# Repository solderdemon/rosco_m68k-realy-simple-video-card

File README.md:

# SolderDemon m68k Really Simple Video

## Overview

A SolderDemon m68k expansion card with a 640 × 480 monochrome framebuffer, 60 Hz VGA output, and two display pages. Two ATF1502AS CPLDs handle video timing, memory addressing, and the host interface.

J1 matches the expansion bus pinout of [rosco_m68k r2](https://github.com/rosco-m68k/rosco_m68k).

**Status.** r1 fabrication files and CPLD programming files are available. The CPLD fit and logic have been verified. Hardware verification is pending.

## Start here

- [KiCad project](design/solderdemon_m68k-realy-simple-video-card.kicad_pro)
- [Schematic (PDF)](manufacturing/solderdemon_m68k-realy-simple-video-card-schematic.pdf)
- [Assembly and bring-up](docs/BRINGUP.md)
- [Gerbers and drill files](manufacturing/solderdemon_m68k-realy-simple-video-card-gerbers.zip)

## Board views

| Top | Bottom |
|:---:|:---:|
|  |  |

## Hardware

### Features

| | |
|---|---|
| Picture | 640 × 480, 1 bit per pixel, two pages; 80 × 60 characters of 8 × 8 |
| Video signal | VGA, 31.25 kHz / 59.5 Hz from a 25.000 MHz can — VESA 640 × 480 @ 60 Hz geometry, 0.7 % slow |
| VRAM | `$A00001 + 2n`, byte n = page << 16 \| y << 7 \| x >> 3; byte access through `/LDS`, no wait states |
| Register | `$B00001` — write b0 video on, b1 page shown; read b0 VBLANK, b1 HBLANK |
| Logic | 2 × ATF1502AS-10JU44 (PLCC-44), one JTAG chain on `J3`; address multiplexer inside |
| Memory | one AS6C1008 128K SRAM, 55–100 ns |
| Data path | 74HCT245 transceiver, 74HC166 serialiser, 2N3904 video buffer |
| Power | 5 V from the bus, ~120–200 mA |
| Assembly | through-hole, every IC socketed; two CPLDs to program over JTAG |
| Size | 92 × 96 mm, 2 layers |

### Two CPLDs, five ICs

An ATF1502AS has 32 macrocells and, with JTAG left enabled, 28 I/O pins plus 4 dedicated inputs —
**32 usable signals**. An address multiplexer alone is 16 inputs plus 16 outputs: 32 pins before
any logic. The card therefore **splits the counters along with the multiplexer halves**, so that
no counter bit ever crosses between the two devices:

| | Holds | Drives | Pins | Macrocells |
|:---|:---|:---|:---:|:---:|
| **U1** | byte counter B, pixel phase, bus decode, control bit "video on", status | MA0–MA6, /HSYNC, /LOAD, /SEL, /SRAM_WE, /BUF_OE, /DTACK, D0, D1 | 32/32 | 30/32 |
| **U2** | line counter L, page register | MA7–MA16, /VSYNC, VBLANK | 30/32 | 30/32 |

Only three wires run between them: `SEL_N`, `LEND` (step the line counter) and `VBLANK`.

- **The control register is synchronous.** It is sampled on every 25 MHz clock while the write
  strobe is low, so it does not depend on the 68010's data hold time.
- **The address path is short.** The CPU's address reaches the SRAM through one CPLD (~10 ns),
  and the video address never leaves the chip that counts it.

### Display and memory

- **Video mode:** 640 × 480 @ 59.52 Hz, 31.250 kHz, exact VESA timing from a 25.000 MHz canned
  oscillator (`X1`) — 16/96/48 clock porches, VSYNC on lines 490-491; the clock leaves `X1`
  through two 33 Ω series resistors (`R7` to the CPLDs, `R8` to `U5`)
- **Framebuffer:** two pages of 480 × 128 bytes in one AS6C1008 (`U3`)
- **Direct CPU access:** VRAM at `$A00001 + 2n` (n = page << 16 | y << 7 | x >> 3), byte access
  through `/LDS`, zero wait states; the CPU reaches both pages at any time
- **Control & status:** one register at `$B00001` — write video on/off and the displayed page,
  read VBLANK and HBLANK
- **Programmable logic:** 2 × ATF1502AS-10JU44 (`U1`, `U2`) in one JTAG chain on `J3`
- **Data path:** 74HCT245 transceiver (`U4`), 74HC166 pixel serialiser (`U5`), `Q1` video emitter follower
- **Video output:** the pixel bit drives `Q1`, an emitter follower, which feeds R, G and B through
  390 Ω (`R1`–`R3`, ~0.67 V into 75 Ω); 47 Ω sync resistors (`R4`, `R5`) to a DE-15 HD socket
  (`J2`). Fit only `R2` for a green screen, `R1` + `R2` for amber — the brightness does not change
- **Power:** +5 V from the expansion bus, ~120–200 mA; 100 nF bypass at every IC (`C1`–`C8`),
  47 µF bulk capacitor (`C9`)
- **Form factor:** 92 × 96 mm 2-layer PCB, right-angle bus socket (`J1`) along the right edge

### Pinout

#### J1 — SolderDemon m68k Expansion Bus (signals used by the card)

| Pin | Signal | Use | Pin | Signal | Use |
|:---:|:---|:---|:---:|:---|:---|
| **1–13 (odd)** | **A1–A7** | to U1, the low address half | **2** | **VCC** | +5 V supply |
| **15–33 (odd)** | **A8–A17** | to U2, the high address half | **6** | **GND** | Ground |
| **39** | **A20** | VRAM (0) / register (1) select | **18** | **~EXPSEL** | Expansion space select (includes `/AS`) |
| **41, 45** | **A21, A23** | Card window decode | **32** | **~LDS** | Byte data strobe |
| **61, 63, 64, 62** | **D0–D3** | Data bus via `U4` | **36** | **~RESET** | Clears the control register |
| **60, 58, 56, 54** | **D4–D7** | Data bus via `U4` | **59** | **R/~W** | Read / write |
| **57** | **~DTACK** | Pulled low by `U1` | | | |

A22 is not decoded (under `/EXPSEL` the only range with A23 and A21 set is `$A00000-$BFFFFF`), and
A18/A19 are unconnected, so the VRAM image repeats through `$A40000–$AFFFFF`.

#### J2 — VGA (DE-15 HD, female)

| Pin | Signal | Description |
|:---:|:---|:---|
| **1, 2, 3** | **RED, GREEN, BLUE** | ~0.62 V into 75 Ω, all three from the same pixel bit |
| **13, 14** | **HSYNC, VSYNC** | Active low, 47 Ω series resistors |
| **5–8, 10, shell** | **GND** | Ground |
| **4, 9, 11, 12, 15** | — | Not connected (no DDC) |

#### J3 — JTAG (Atmel 10-pin ISP)

| Pin | Signal | Pin | Signal |
|:---:|:---|:---:|:---|
| 1 | TCK | 2 | GND |
| 3 | TDO | 4 | VCC (+5 V) |
| 5 | TMS | 6–8 | not connected |
| 9 | TDI | 10 | GND |

The two devices sit in one chain: TDI → U1 → U2 → TDO.

#### Memory map

| Address | R/W | Description |
|:---|:---:|:---|
| `$A00001 + 2n` | R/W | VRAM byte n = page << 16 \| y << 7 \| x >> 3 (128 bytes per row, 80 visible; bit 7 is the leftmost pixel) |
| `$B00001` | W | b0 video on, b1 page shown; system reset clears both (black screen, page 0) |
| `$B00001` | R | b0 VBLANK, b1 HBLANK (1 = in blanking); b2–b7 undefined, mask them |

The register repeats over `$B00001–$BFFFFF`. Even addresses in `$A00000–$BFFFFF` end in a bus
error. Any CPU access while the picture is on shows eight wrong pixels on the current scanline
("snow"), so draw on the hidden page and `video_flip()`, or draw inside VBLANK.

This window does not overlap `rosco_m68k-simple-video` (`$800000–$9FFFFF`), so both cards can sit
on the same backplane. Check it against your RAM expansion, which also lives in expansion space.

## Using the board

### Software

```c
#include "video.h"

video_init();                                   /* video off, page 0 */
video_clear(0);
video_text(2, 2, "SolderDemon m68k Really Simple Video");
video_rect(0, 0, 640, 480, 1);
video_show(0, true);

video_draw_page(1);                             /* draw on the hidden page... */
video_clear(0);
video_fill(100, 80, 96, 64, 1);
video_flip();                                   /* ...and show it at the next VBLANK */
```

Without the driver, `*(uint8_t *)(0xA00001 + (y << 8) + ((x >> 3) << 1)) |= 0x80 >> (x & 7);`
sets a pixel on page 0. The driver (`code/software/video.c/.h`) adds clipping, lines, fills, an 8 × 8
console font (80 × 60 characters), page flipping and a full VRAM self test; `code/software/main.c` is a
text-page and bouncing-box demo.

## Build and verification

### Bill of Materials

| Reference | Value | Package / Footprint | Notes |
|:---|:---|:---|:---|
| **U1** | ATF1502AS-10JU44 | PLCC-44, THT socket | Bus, byte counter, MA0–MA6 — `code/firmware/cpld/rsv_u1.pld` |
| **U2** | ATF1502AS-10JU44 | PLCC-44, THT socket | Line counter, MA7–MA16, page — `code/firmware/cpld/rsv_u2.pld` |
| **U3** | AS6C1008-55PCN | DIP-32, 600 mil | 128K SRAM, 55–100 ns |
| **U4** | 74HCT245 | DIP-20 | Data bus transceiver |
| **U5** | 74HC166 | DIP-16 | Pixel serialiser |
| **X1** | 25.000 MHz | Oscillator DIP-8, 5 V | Canned oscillator (not a crystal) |
| **J1** | Conn_02x32 | PinSocket 2×32, 2.54 mm, Horizontal | SolderDemon m68k expansion bus |
| **J2** | DE-15 HD | DSUB-15-HD Socket, Horizontal | VGA output |
| **J3** | 2×5 pin header | 2.54 mm | Atmel JTAG / ISP |
| **Q1** | 2N3904 | TO-92 | Video emitter follower (BC547, BC337, 2N2222 all fine) |
| **R1–R3** | 390 Ω | Axial DIN0207, P7.62 mm | Video R, G, B |
| **R6** | 220 Ω | Axial DIN0207, P7.62 mm | Base resistor for Q1 |
| **R4, R5** | 47 Ω | Axial DIN0207, P7.62 mm | HSYNC / VSYNC series resistors |
| **R7, R8** | 33 Ω | Axial DIN0207, P7.62 mm | Clock series resistors at X1: R7 to the CPLDs, R8 to U5 |
| **C1–C8** | 100 nF | Radial 5.08 mm pitch | Bypass: two per CPLD, one per other IC, one at the oscillator |
| **C9** | 47 µF 10 V | Radial D6.3 mm, P2.5 mm | Bulk capacitor |
| — | Sockets | 2 × PLCC-44 THT, 1 × DIP-32 (600 mil), 1 × DIP-20, 1 × DIP-16, 1 × DIP-8 | Every IC is socketed |

You will also need a **JTAG programmer** — a USB Blaster clone is enough — and Microchip's WinCUPL
plus the ATF150x fitter.

The shift register stays discrete because neither CPLD has eight spare pins for MD0–MD7. It is an
ordinary **74HC166**: Nexperia specify that part at 40 MHz over the full temperature range at
4.5 V, so 25.000 MHz has plenty of margin.

Three 75 Ω monitor inputs want 9.3 mA each at full white, about 26 mA from one driver, and no
74HC/HCT output is rated for that (74HC166: IOH 4 mA, 20 mA absolute maximum). So `Q1` is an
emitter follower: U5 drives its base through `R6` at a few hundred microamps and `Q1` supplies the
current. `R1`–`R3` then set the level on their own, which is why leaving one out changes the
colour but not the brightness.

### Design files

- **KiCad project:** `design/solderdemon_m68k-realy-simple-video-card.kicad_pro` / `.kicad_sch` / `.kicad_pcb`
- **CPLD firmware:** [code/firmware/cpld/rsv_u1.pld](code/firmware/cpld/rsv_u1.pld), [code/firmware/cpld/rsv_u2.pld](code/firmware/cpld/rsv_u2.pld) —
  CUPL sources; they are also the single source of each CPLD's pinout, read by the generator and
  the simulator
- **Manufacturing outputs:** [manufacturing/](manufacturing) — Gerbers, drill file, placement
  file, schematic PDF, BOM
- **PCB specs:** 2 layers, 92 × 96 mm, 1.6 mm FR-4, 1 oz copper, 0.2 mm minimum track and
  clearance, 0.3 mm minimum hole, GND pour on both layers
- **Software:** [code/software/](code/software) — driver `video.c/.h`, font `font8x8.c`, demo `main.c`,
  Makefile; [code/tests/test_driver.c](code/tests/test_driver.c) host test
- **Generators:** [tools/](tools) — `build_card.py`, `route_card.py`, `sim_card.py` + `cupl.py`,
  `make_font.py`
- **Design documentation:** [docs/DESIGN.md](docs/DESIGN.md) (how the split works),
  [docs/BRINGUP.md](docs/BRINGUP.md) (programming, assembly, first power-up),
  [docs/BUILD.md](docs/BUILD.md) (regenerating everything)

### Verification

- **ERC:** 0 errors, 0 warnings ([erc.rpt](erc.rpt)).
- **DRC with schematic parity:** 0 violations at error *and* warning severity, 0 unconnected pads
  ([drc.rpt](drc.rpt)).
- **Routing:** 1154 tracks and vias, 68 vias, GND pour on both layers.
- **Netlist simulation** ([sim-verification.txt](sim-verification.txt), 31/31 pass): both counters
  run their full cycles and recover from all 128/1024 power-up states; the raster is 800 clocks ×
  525 lines with HSYNC at clocks 664–759 and VSYNC on lines 490–491; VRAM writes and reads on both
  pages; the control register split across the two chips, and the status read; `/DTACK` only
  inside the window; no bus contention. Two checks are specific to r1: **MA0..MA16 is compared
  against the expected address on every clock of a frame**, which is what proves the two address
  halves agree, and all 307200 pixels of a frame are compared with the SRAM, then again after a
  page flip. The simulator runs the real `.pld` files through `tools/cupl.py`.
- **CPLD fit** (`code/firmware/cpld/build.sh`, `code/firmware/cpld/bin/*.fit`, `*.jed`): both designs fit with every pin where
  the `.pld` — and therefore the PCB — puts it; U1 32/32 pins and 30/32 macrocells, U2 30/32 and
  30/32. `tools/check_fit.py` then compares the fitter's sum-of-products equations with the
  `cupl.py` model the simulation ran (every output, enable and next state, 200000 random vectors
  each): they match. This check found that CUPL reads `!FIELD:[lo..hi]` as "the complemented
  field is in range", which had turned both sync pulses into nonsense in the compiled logic while
  the simulation passed; the `.pld` files now write `!(FIELD:[..])` and `cupl.py` follows CUPL.
- **Driver** ([driver-verification.txt](driver-verification.txt), 31/31 pass): the real `video.c`
  against a model of the card, including the self test catching a stuck page address line.
- **NOT verified — read this before ordering a board:**
  - Timing has only been checked on paper, including the one-clock BUFD delay that lets the SRAM
    and the 74HCT245 share MD, and the LEND hand-off between the two chips.
  - No PCB has been manufactured; no build with the m68k toolchain; monitor compatibility unknown.

<!-- repository-layout -->
## Repository layout

- [`design/`](design/solderdemon_m68k-realy-simple-video-card.kicad_pro): KiCad project, schematic sheets, PCB, local libraries and design data. Open the project directly here.
- [`code/firmware/`](code/firmware/): ROM and programmable-logic sources and programming files.
- [`code/software/`](code/software/): drivers, examples and applications.
- [`code/build/`](code/build/): local build products; ignored by Git except for its README.
- [`tools/`](tools/): generators, simulations and export scripts. Run commands from the repository root unless stated otherwise.
- [`manufacturing/`](manufacturing/): fabrication packages.

Programmable-logic files are in `code/firmware/cpld/`. Native CPLD tools retain their adjacent `bin/` outputs.
Design files and documentation are generated by scripts in `tools/`; change the sources and regenerate. Keep `.kicad_pro` as the source of DRC rules.
<!-- /repository-layout -->

## Licences and attribution

Copyright © 2026 SolderDemon.

- **Hardware** — [CERN Open Hardware Licence v1.2](LICENCE.hardware.txt).
- **Documentation** — [Creative Commons Attribution 4.0](https://creativecommons.org/licenses/by/4.0/).

Third-party materials retain their original notices and licence terms.

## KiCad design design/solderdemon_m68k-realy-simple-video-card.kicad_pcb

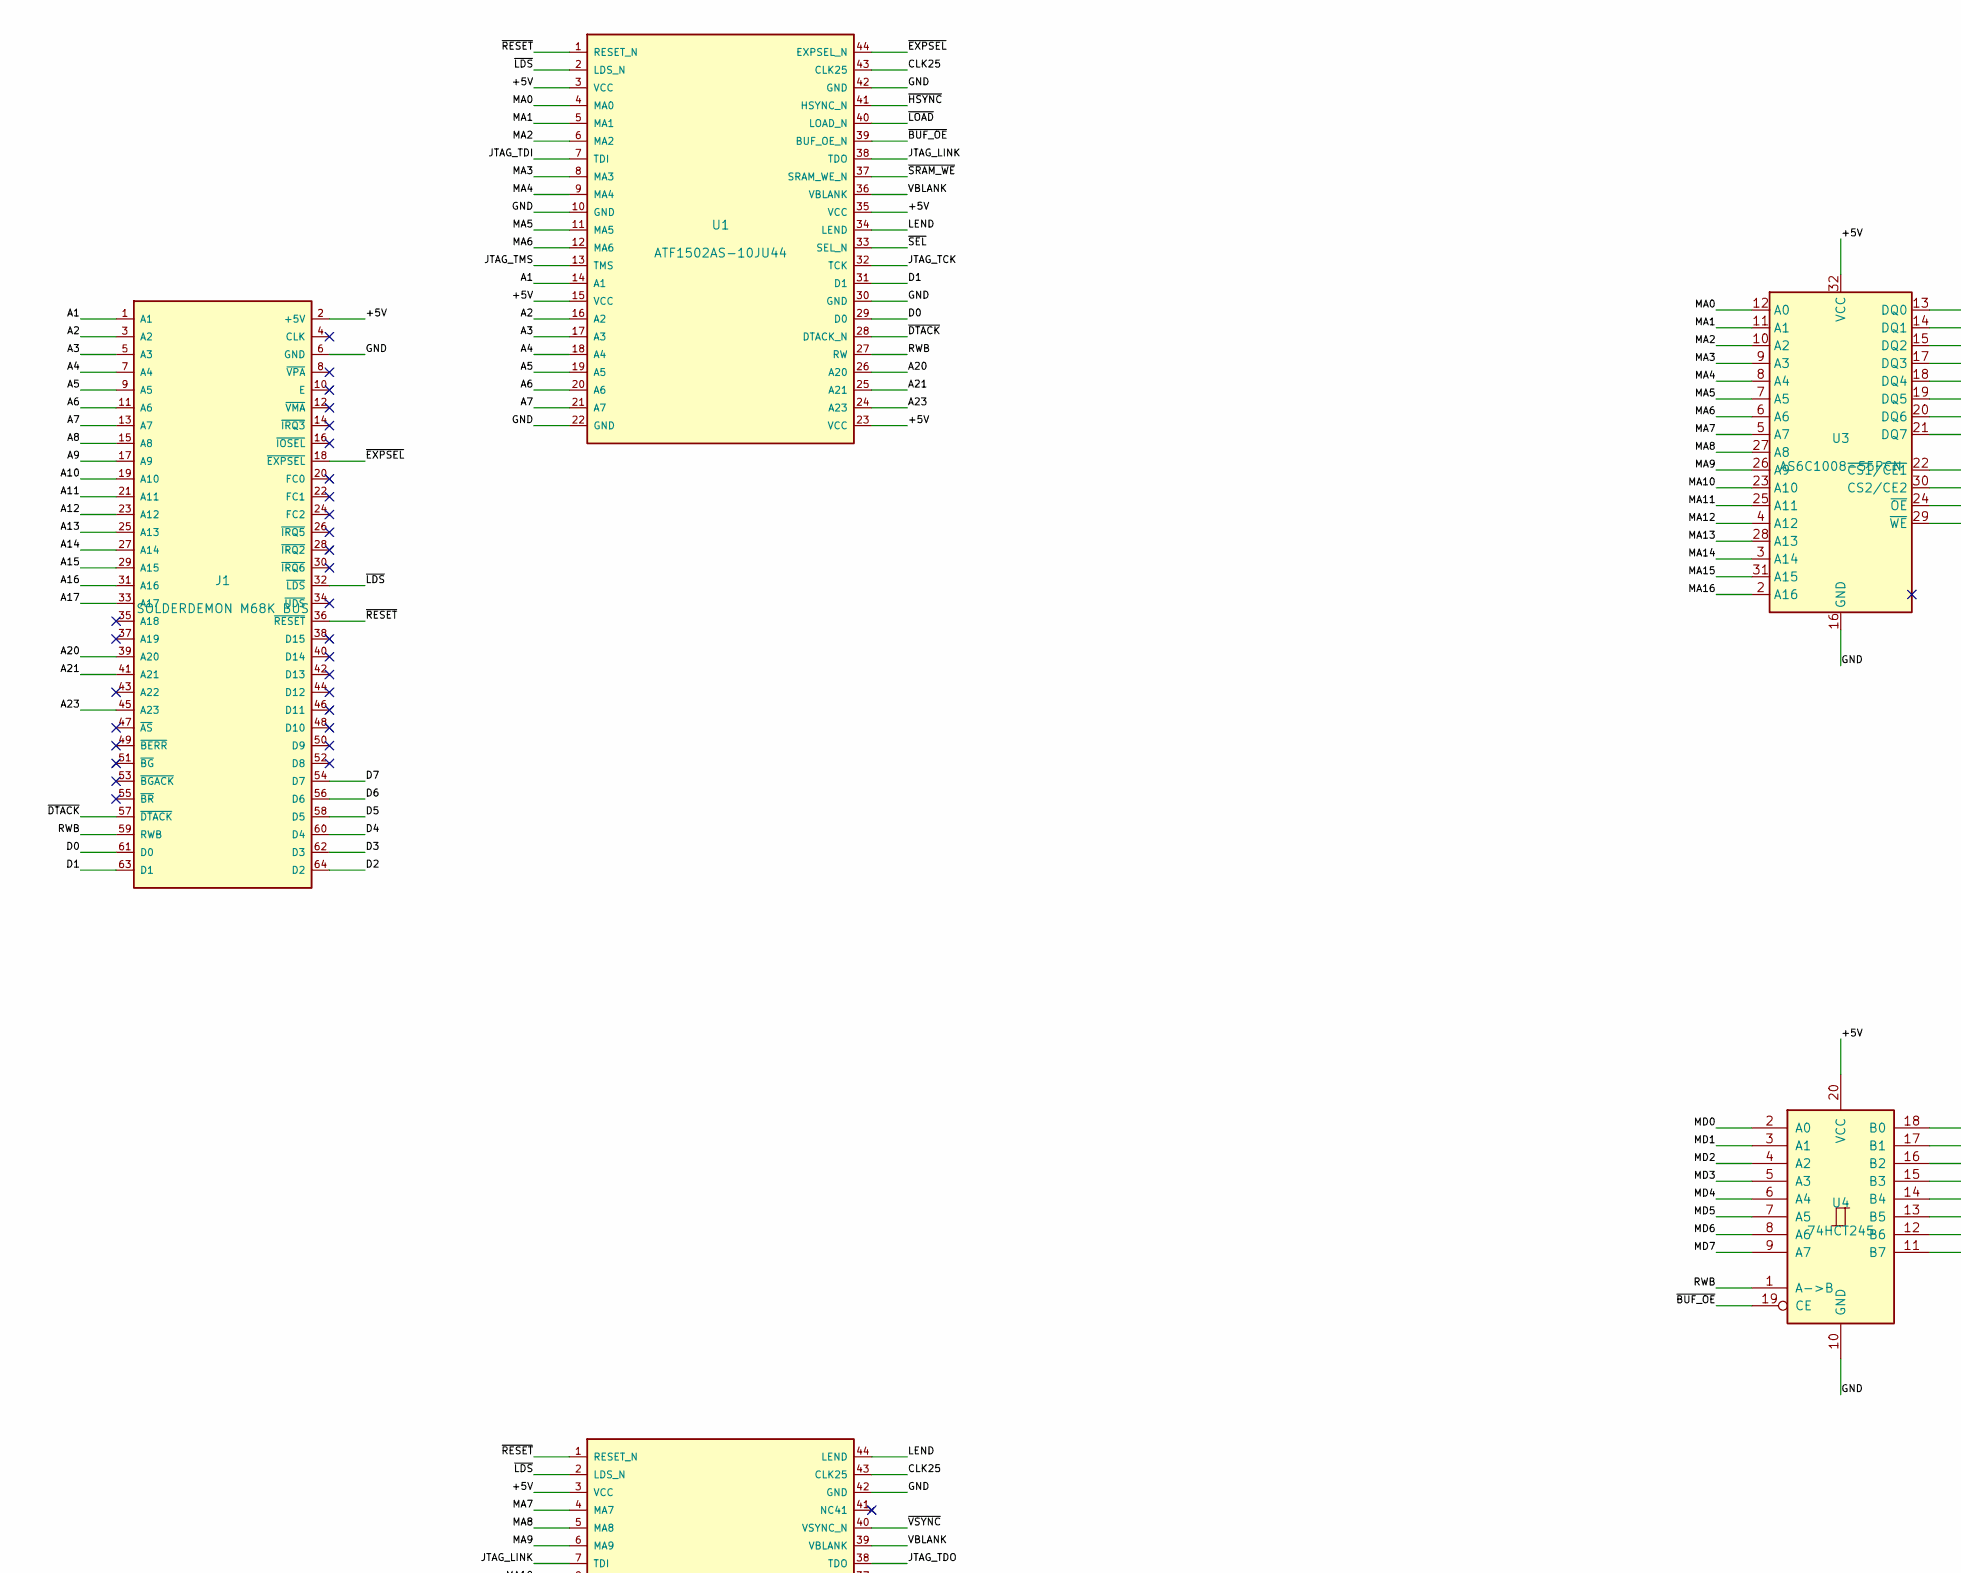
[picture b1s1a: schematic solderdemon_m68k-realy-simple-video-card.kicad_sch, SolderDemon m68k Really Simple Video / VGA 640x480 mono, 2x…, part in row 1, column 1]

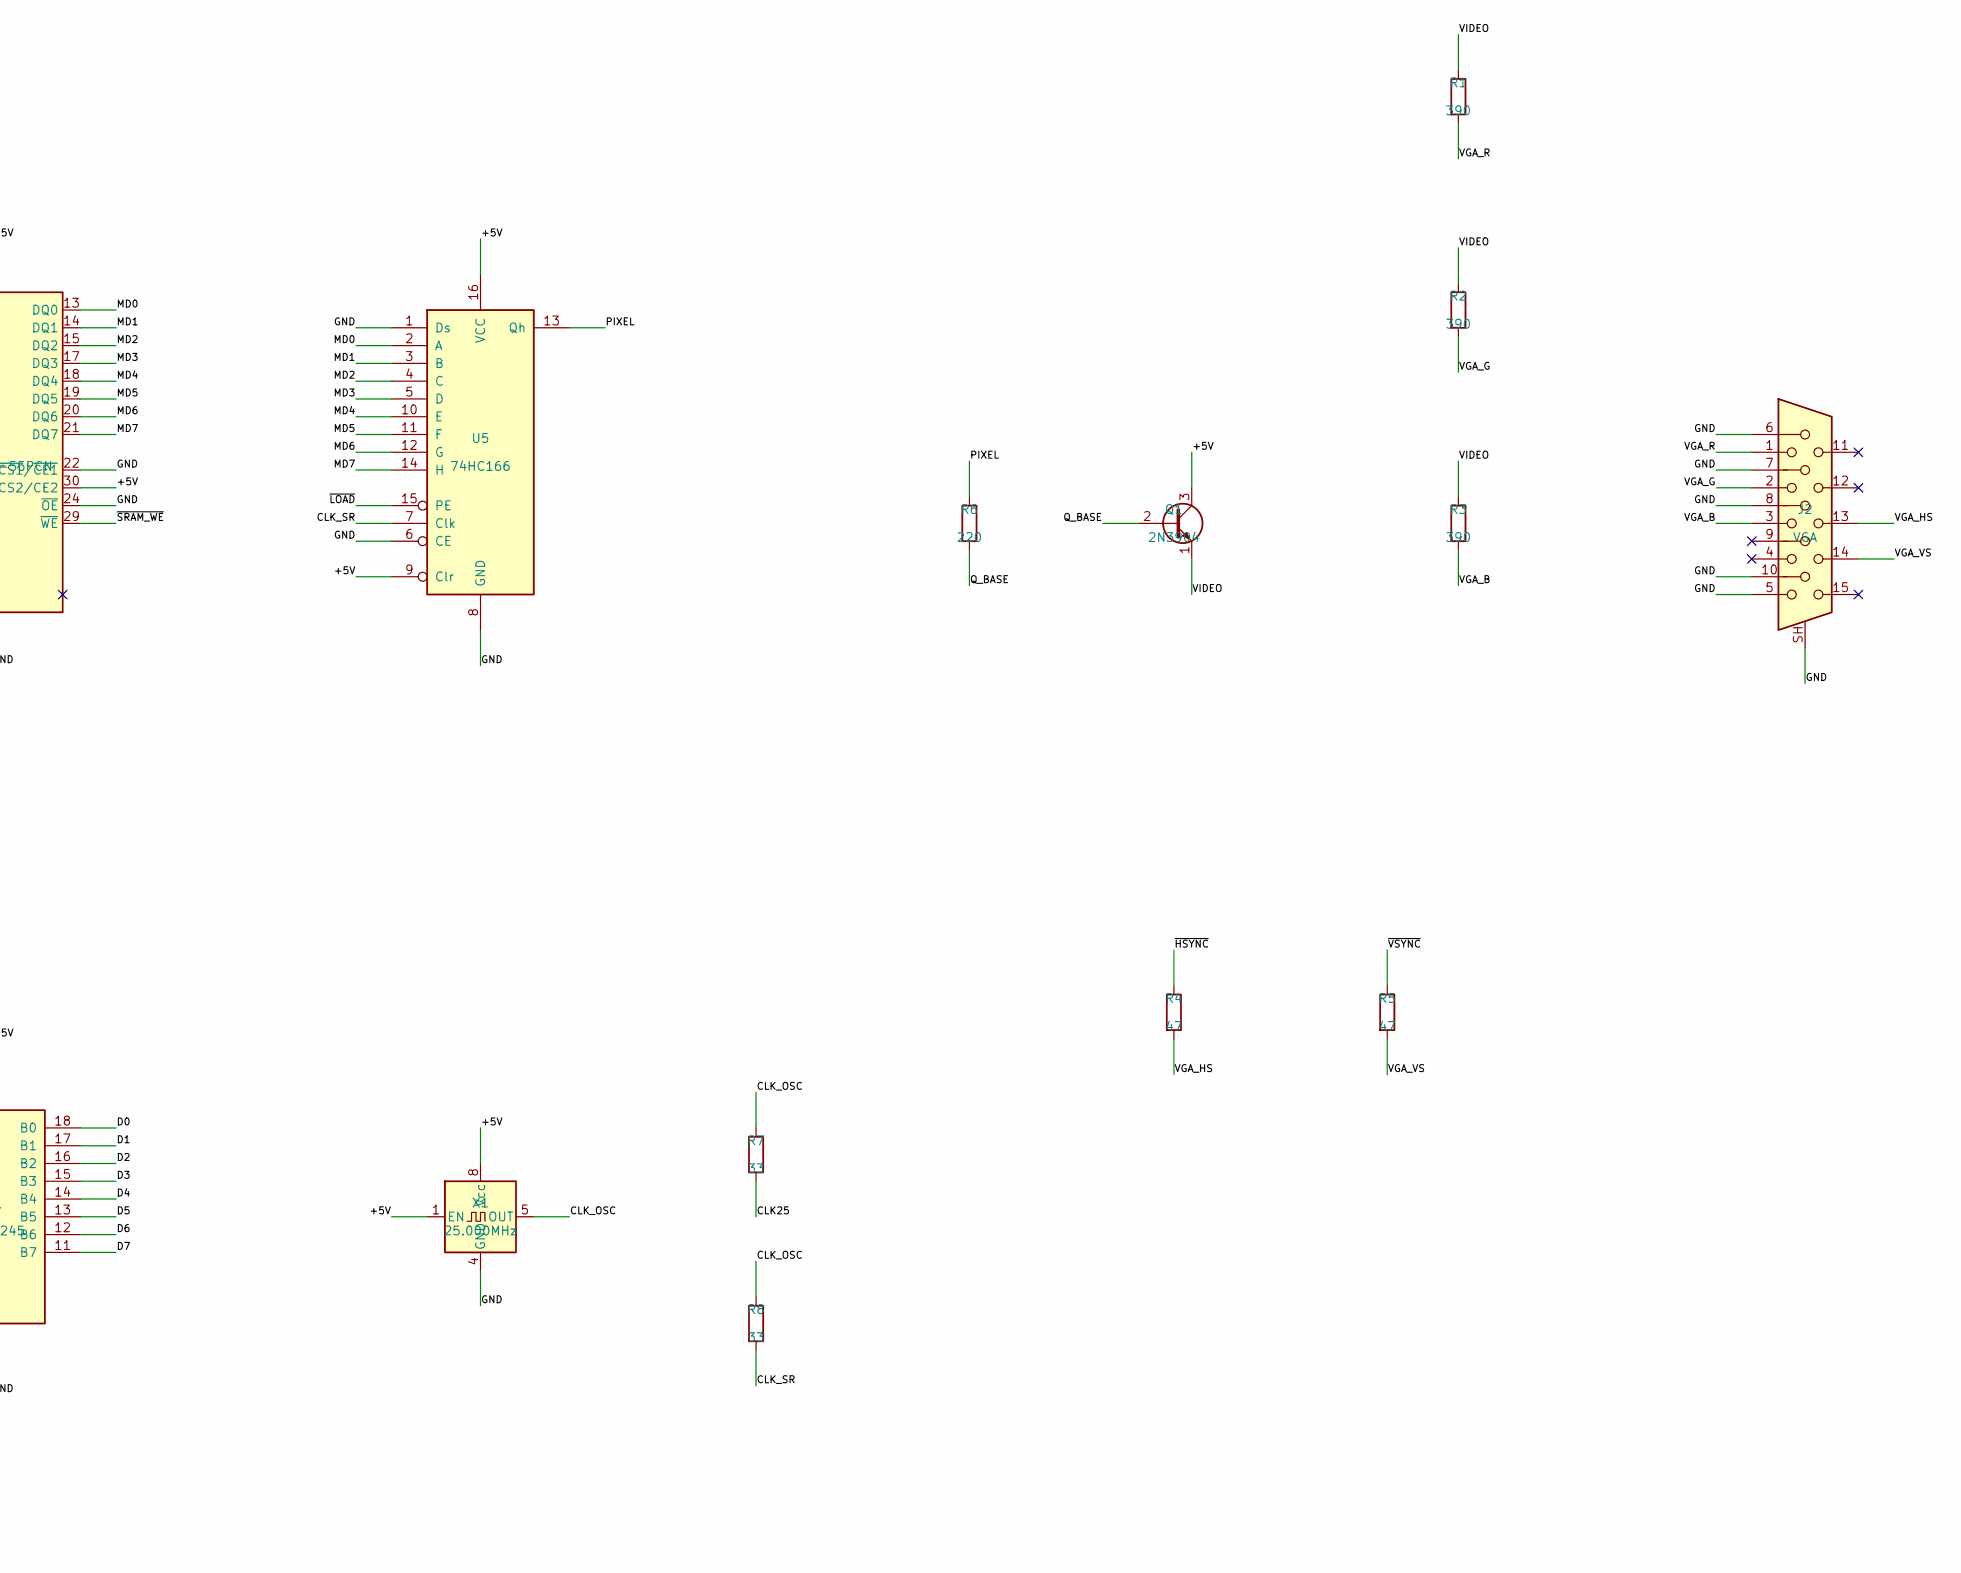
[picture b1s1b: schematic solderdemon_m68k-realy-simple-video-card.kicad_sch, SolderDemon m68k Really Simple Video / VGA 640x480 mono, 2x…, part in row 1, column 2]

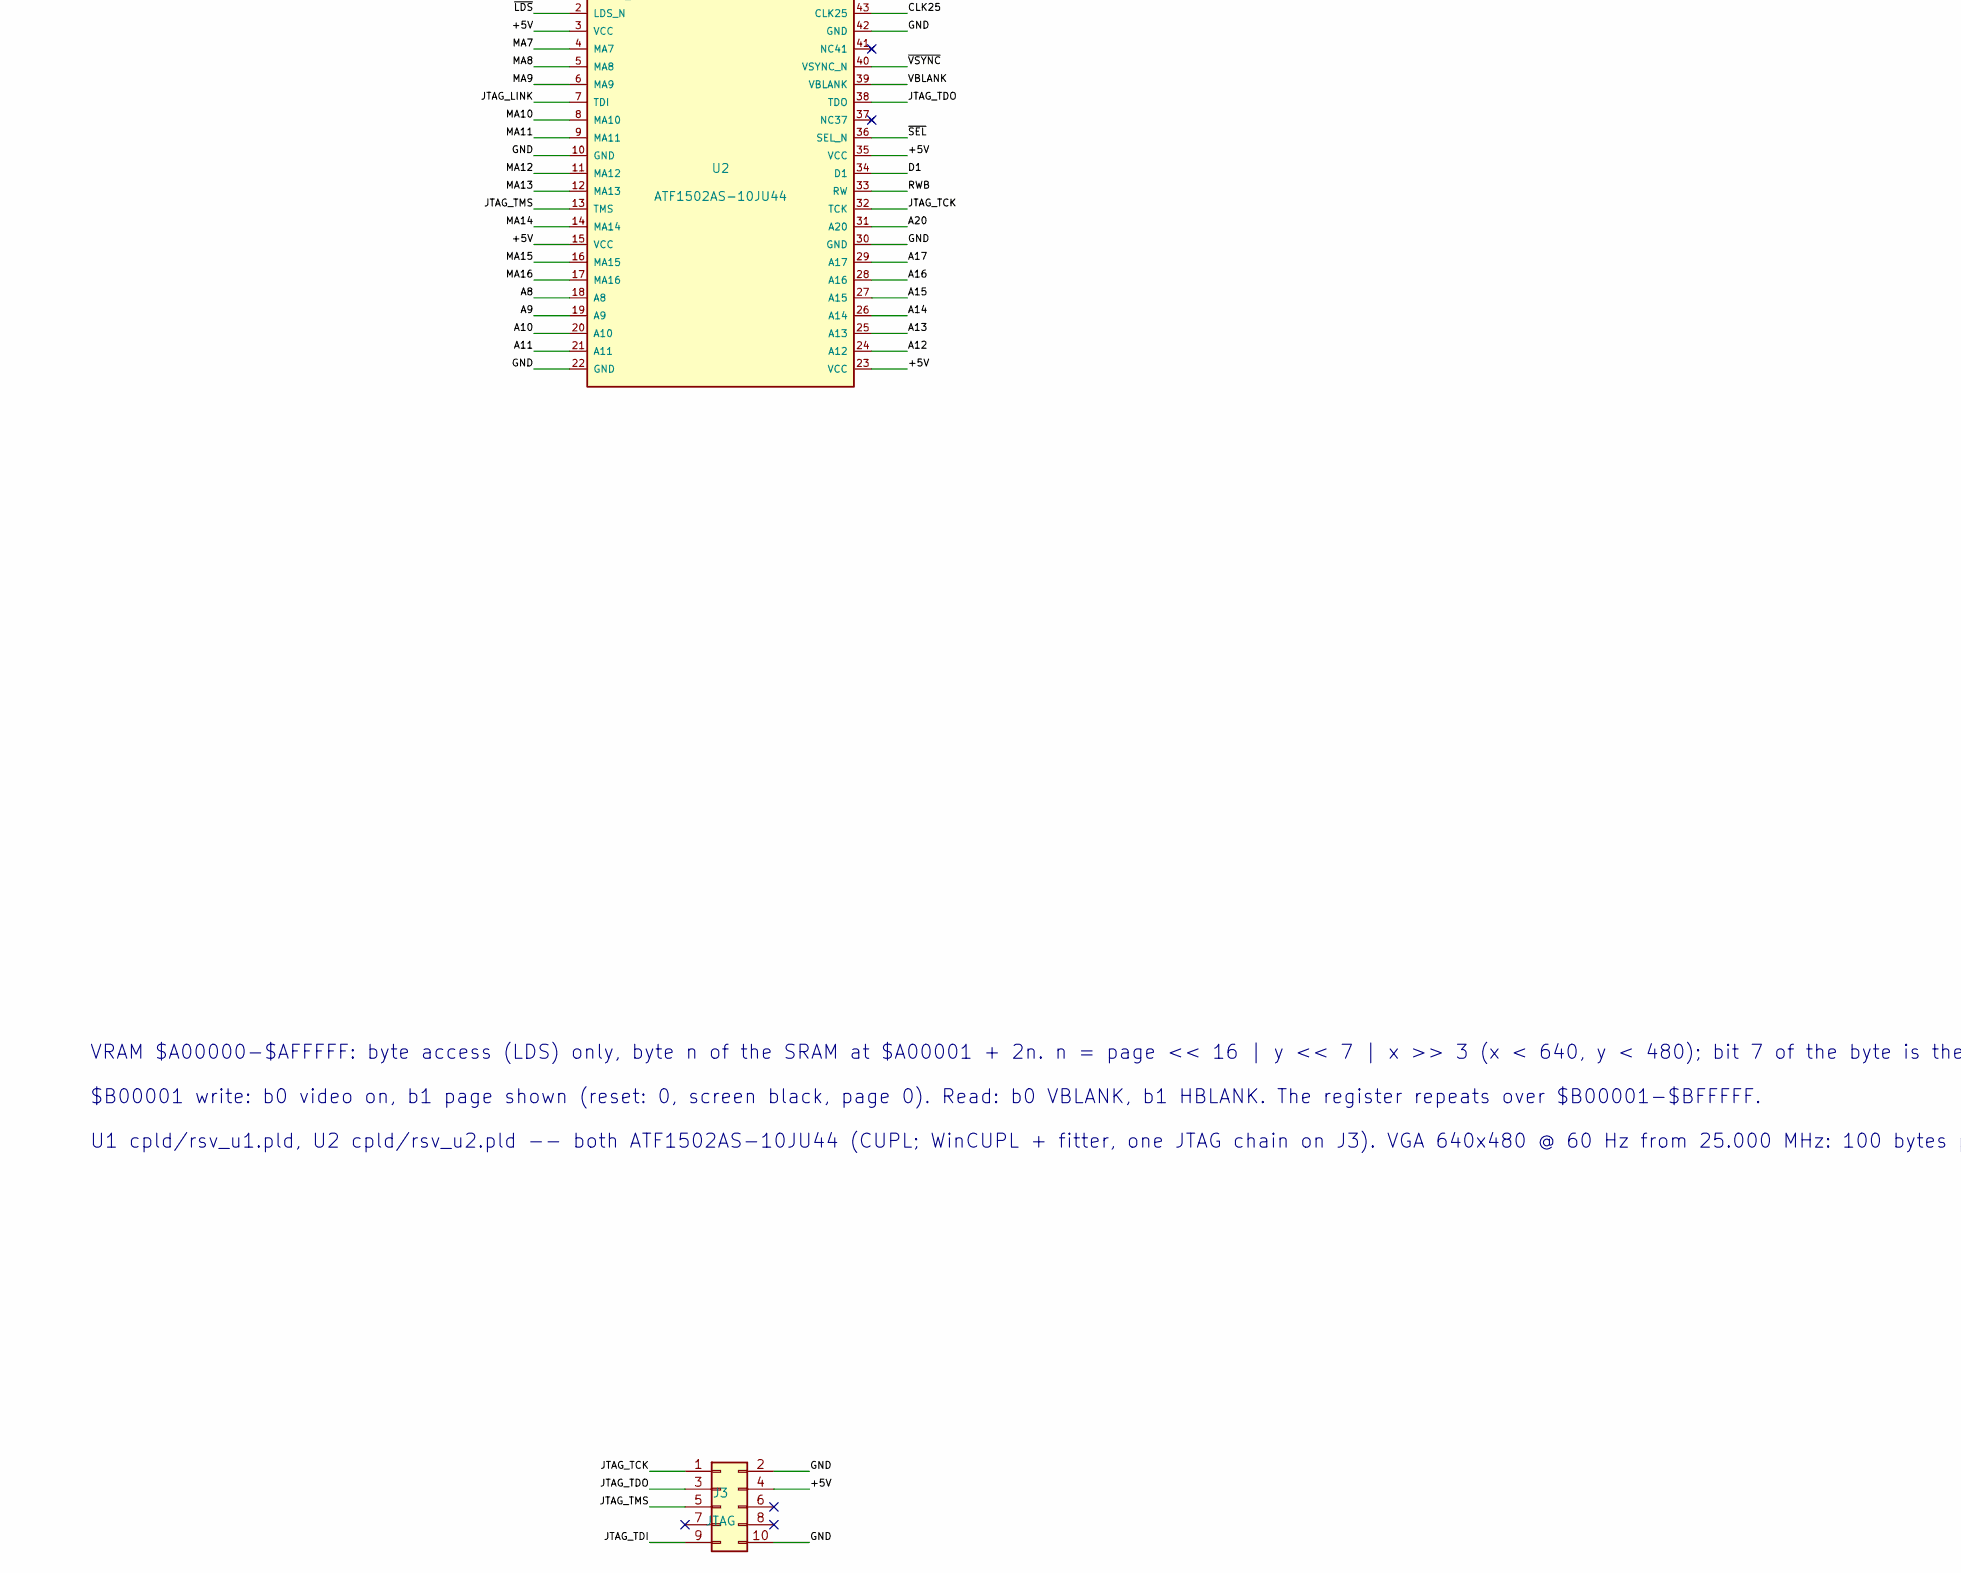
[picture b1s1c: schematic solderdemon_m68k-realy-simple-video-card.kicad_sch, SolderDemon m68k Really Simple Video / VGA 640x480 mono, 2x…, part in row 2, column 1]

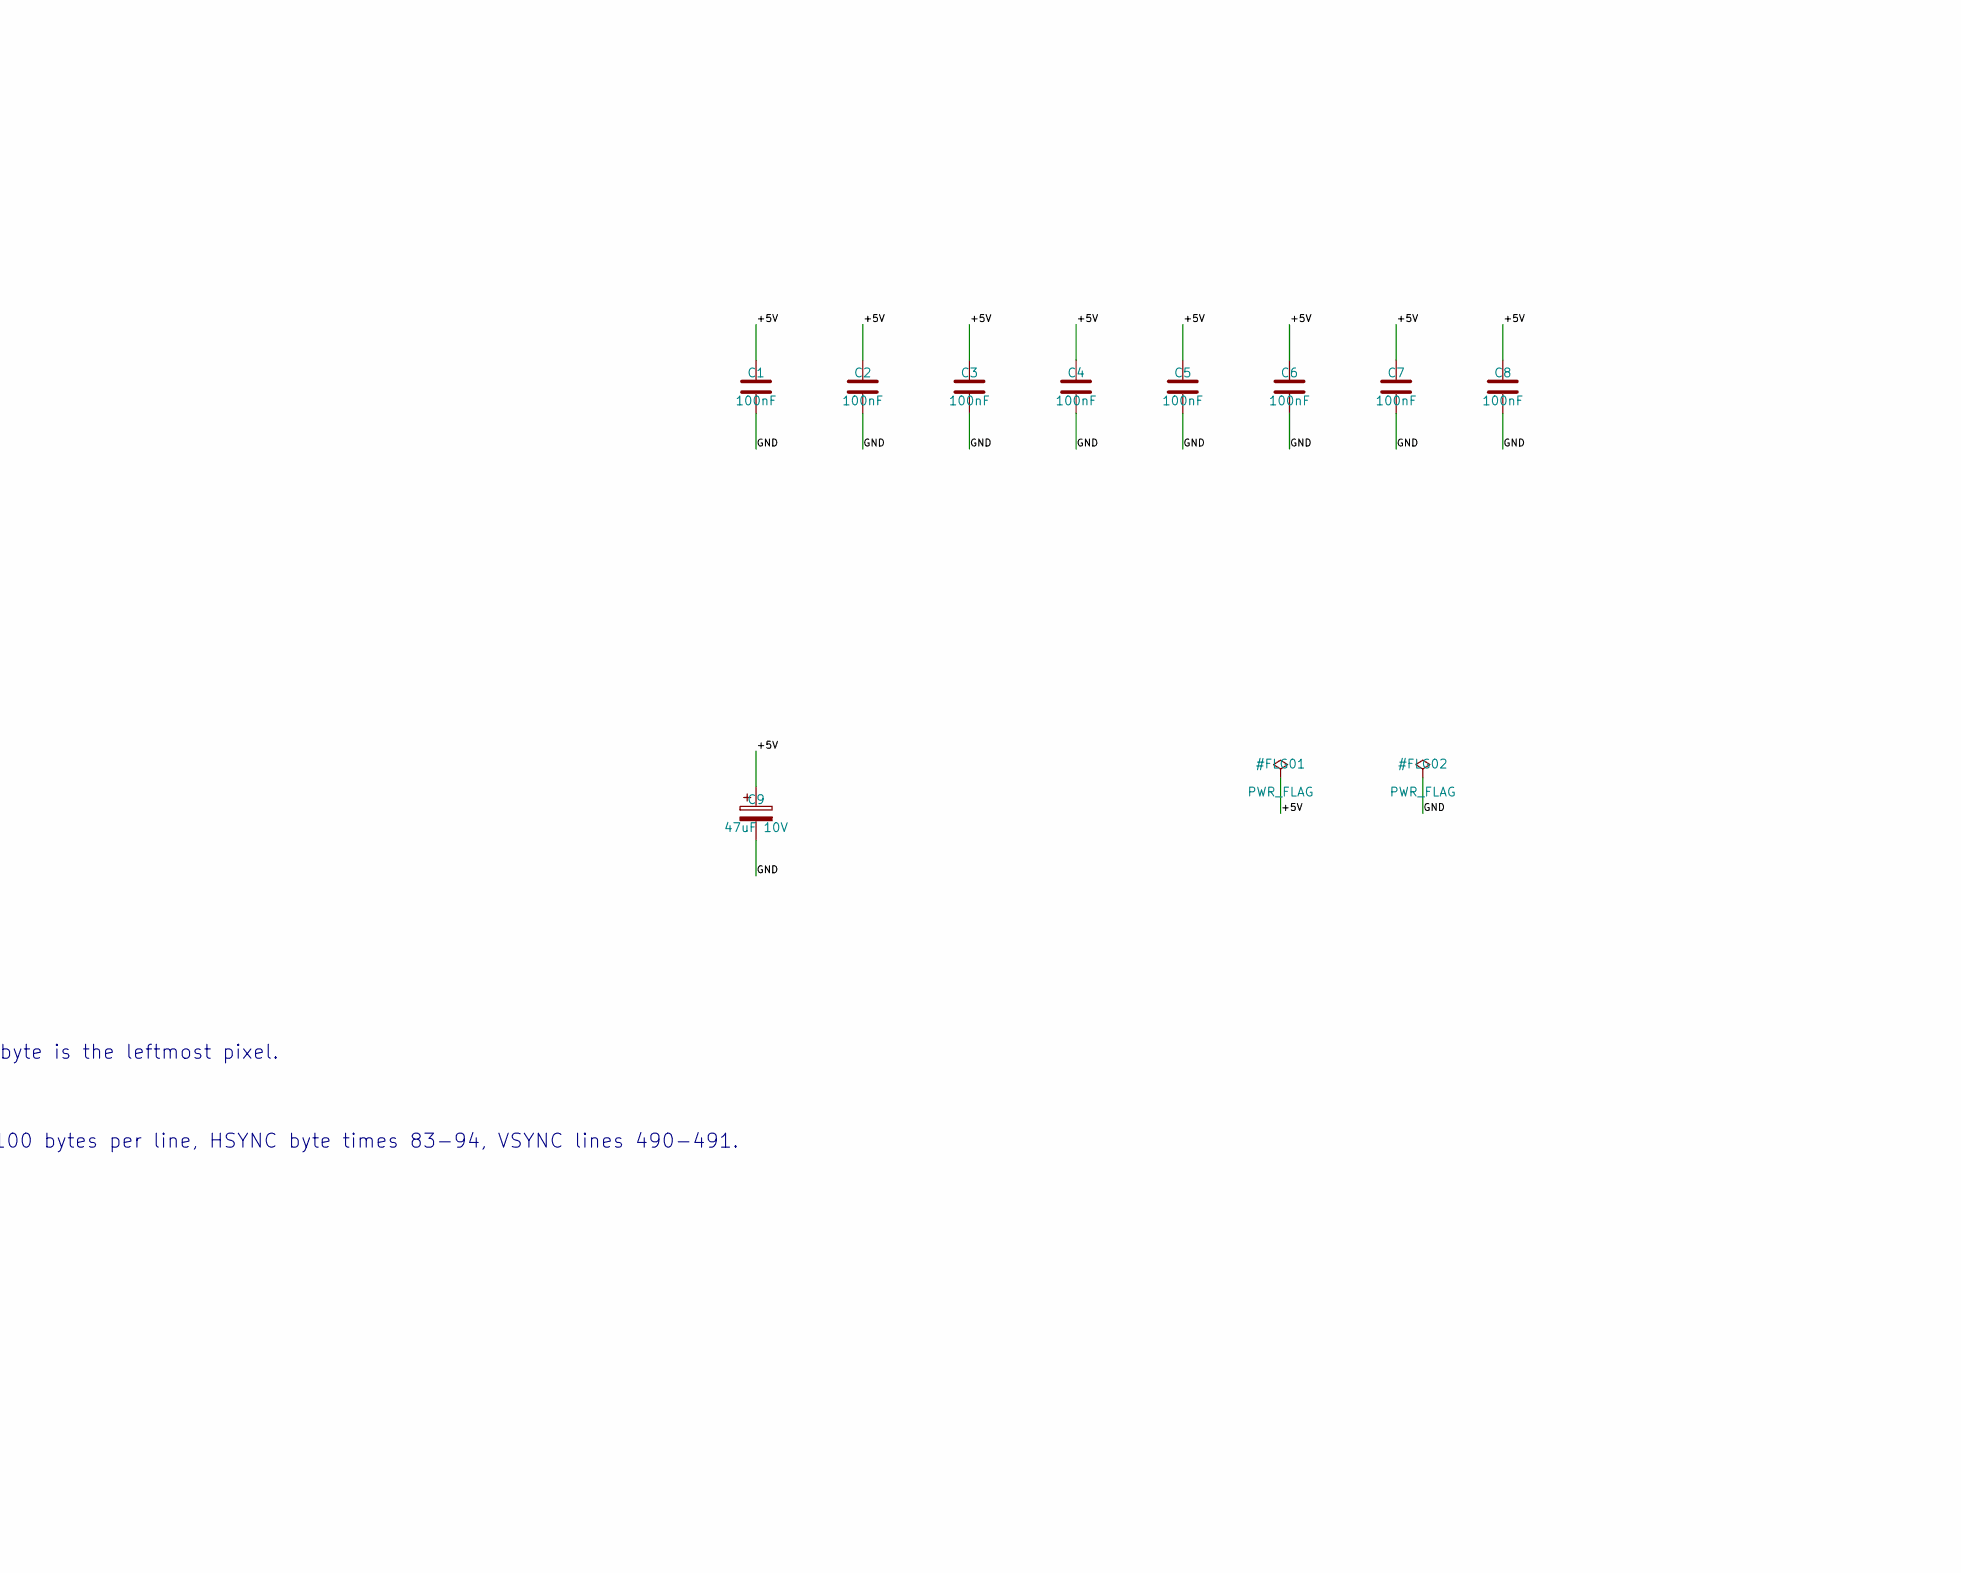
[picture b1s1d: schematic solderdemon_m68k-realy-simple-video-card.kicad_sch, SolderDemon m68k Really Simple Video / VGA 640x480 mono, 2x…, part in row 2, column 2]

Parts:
C1, C2, C3, C4, C5, C6, C7, C8: 100nF; C_Radial_5.08mm
C9: 47uF 10V; CP_Radial_D6.3mm_P2.50mm
J1: SOLDERDEMON M68K BUS; PinSocket_2x32_P2.54mm_Horizontal_CardEdge
J2: VGA; DSUB-15-HD_Socket_Horizontal_P2.29x1.90mm_EdgePinOffset3.03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
J3: JTAG; PinHeader_2x05_P2.54mm_Vertical
Q1: 2N3904; TO-92_Inline
R1, R2, R3: 390; R_Axial_DIN0207_L6.3mm_D2.5mm_P7.62mm_Horizontal
R4, R5: 47; R_Axial_DIN0207_L6.3mm_D2.5mm_P7.62mm_Horizontal
R6: 220; R_Axial_DIN0207_L6.3mm_D2.5mm_P7.62mm_Horizontal
R7, R8: 33; R_Axial_DIN0207_L6.3mm_D2.5mm_P7.62mm_Horizontal
U1, U2: ATF1502AS-10JU44; PLCC-44_THT-Socket
U3: AS6C1008-55PCN; DIP-32_W15.24mm_Socket_LongPads
U4: 74HCT245; DIP-20_W7.62mm_Socket_LongPads
U5: 74HC166; DIP-16_W7.62mm_Socket_LongPads
X1: 25.000MHz; Oscillator_DIP-8

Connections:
/+5V: C1.1, C2.1, C3.1, C4.1, C5.1, C6.1, C7.1, C8.1, C9.1, J1.2 (+5V), J3.4, Q1.3 (C), U1.3 (VCC), U1.15 (VCC), U1.23 (VCC), U1.35 (VCC), U2.3 (VCC), U2.15 (VCC), U2.23 (VCC), U2.35 (VCC), U3.30 (CS2/CE2), U3.32 (VCC), U4.20 (VCC), U5.9 (Clr), U5.16 (VCC), X1.1 (EN), X1.8 (Vcc)
/A1: J1.1 (A1), U1.14 (A1)
/A2: J1.3 (A2), U1.16 (A2)
/A3: J1.5 (A3), U1.17 (A3)
/A4: J1.7 (A4), U1.18 (A4)
/A5: J1.9 (A5), U1.19 (A5)
/A6: J1.11 (A6), U1.20 (A6)
/A7: J1.13 (A7), U1.21 (A7)
/A8: J1.15 (A8), U2.18 (A8)
/A9: J1.17 (A9), U2.19 (A9)
/A10: J1.19 (A10), U2.20 (A10)
/A11: J1.21 (A11), U2.21 (A11)
/A12: J1.23 (A12), U2.24 (A12)
/A13: J1.25 (A13), U2.25 (A13)
/A14: J1.27 (A14), U2.26 (A14)
/A15: J1.29 (A15), U2.27 (A15)
/A16: J1.31 (A16), U2.28 (A16)
/A17: J1.33 (A17), U2.29 (A17)
/A20: J1.39 (A20), U1.26 (A20), U2.31 (A20)
/A21: J1.41 (A21), U1.25 (A21)
/A23: J1.45 (A23), U1.24 (A23)
/CLK25: R7.2, U1.43 (CLK25), U2.43 (CLK25)
/CLK_OSC: R7.1, R8.1, X1.5 (OUT)
/CLK_SR: R8.2, U5.7 (Clk)
/D0: J1.61 (D0), U1.29 (D0), U4.18 (B0)
/D1: J1.63 (D1), U1.31 (D1), U2.34 (D1), U4.17 (B1)
/D2: J1.64 (D2), U4.16 (B2)
/D3: J1.62 (D3), U4.15 (B3)
/D4: J1.60 (D4), U4.14 (B4)
/D5: J1.58 (D5), U4.13 (B5)
/D6: J1.56 (D6), U4.12 (B6)
/D7: J1.54 (D7), U4.11 (B7)
/GND: C1.2, C2.2, C3.2, C4.2, C5.2, C6.2, C7.2, C8.2, C9.2, J1.6 (GND), J2.5, J2.6, J2.7, J2.8, J2.10, J2.SH, J3.2, J3.10, U1.10 (GND), U1.22 (GND), U1.30 (GND), U1.42 (GND), U2.10 (GND), U2.22 (GND), U2.30 (GND), U2.42 (GND), U3.16 (GND), U3.22 (~CS1/~CE1), U3.24 (~OE), U4.10 (GND), U5.1 (Ds), U5.6 (CE), U5.8 (GND), X1.4 (GND)
/JTAG_LINK: U1.38 (TDO), U2.7 (TDI)
/JTAG_TCK: J3.1, U1.32 (TCK), U2.32 (TCK)
/JTAG_TDI: J3.9, U1.7 (TDI)
/JTAG_TDO: J3.3, U2.38 (TDO)
/JTAG_TMS: J3.5, U1.13 (TMS), U2.13 (TMS)
/LEND: U1.34 (LEND), U2.44 (LEND)
/MA0: U1.4 (MA0), U3.12 (A0)
/MA1: U1.5 (MA1), U3.11 (A1)
/MA2: U1.6 (MA2), U3.10 (A2)
/MA3: U1.8 (MA3), U3.9 (A3)
/MA4: U1.9 (MA4), U3.8 (A4)
/MA5: U1.11 (MA5), U3.7 (A5)
/MA6: U1.12 (MA6), U3.6 (A6)
/MA7: U2.4 (MA7), U3.5 (A7)
/MA8: U2.5 (MA8), U3.27 (A8)
/MA9: U2.6 (MA9), U3.26 (A9)
/MA10: U2.8 (MA10), U3.23 (A10)
/MA11: U2.9 (MA11), U3.25 (A11)
/MA12: U2.11 (MA12), U3.4 (A12)
/MA13: U2.12 (MA13), U3.28 (A13)
/MA14: U2.14 (MA14), U3.3 (A14)
/MA15: U2.16 (MA15), U3.31 (A15)
/MA16: U2.17 (MA16), U3.2 (A16)
/MD0: U3.13 (DQ0), U4.2 (A0), U5.2 (A)
/MD1: U3.14 (DQ1), U4.3 (A1), U5.3 (B)
/MD2: U3.15 (DQ2), U4.4 (A2), U5.4 (C)
/MD3: U3.17 (DQ3), U4.5 (A3), U5.5 (D)
/MD4: U3.18 (DQ4), U4.6 (A4), U5.10 (E)
/MD5: U3.19 (DQ5), U4.7 (A5), U5.11 (F)
/MD6: U3.20 (DQ6), U4.8 (A6), U5.12 (G)
/MD7: U3.21 (DQ7), U4.9 (A7), U5.14 (H)
/PIXEL: R6.1, U5.13 (Qh)
/Q_BASE: Q1.2 (B), R6.2
/RWB: J1.59 (RWB), U1.27 (RW), U2.33 (RW), U4.1 (A->B)
/VBLANK: U1.36 (VBLANK), U2.39 (VBLANK)
/VGA_B: J2.3, R3.2
/VGA_G: J2.2, R2.2
/VGA_HS: J2.13, R4.2
/VGA_R: J2.1, R1.2
/VGA_VS: J2.14, R5.2
/VIDEO: Q1.1 (E), R1.1, R2.1, R3.1
/~BUF_OE: U1.39 (BUF_OE_N), U4.19 (CE)
/~DTACK: J1.57 (~DTACK), U1.28 (DTACK_N)
/~EXPSEL: J1.18 (~EXPSEL), U1.44 (EXPSEL_N)
/~HSYNC: R4.1, U1.41 (HSYNC_N)
/~LDS: J1.32 (~LDS), U1.2 (LDS_N), U2.2 (LDS_N)
/~LOAD: U1.40 (LOAD_N), U5.15 (PE)
/~RESET: J1.36 (~RESET), U1.1 (RESET_N), U2.1 (RESET_N)
/~SEL: U1.33 (SEL_N), U2.36 (SEL_N)
/~SRAM_WE: U1.37 (SRAM_WE_N), U3.29 (~WE)
/~VSYNC: R5.1, U2.40 (VSYNC_N)

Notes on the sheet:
VRAM $A00000-$AFFFFF: byte access (LDS) only, byte n of the SRAM at $A00001 + 2n. n = page << 16 | y << 7 | x >> 3 (x < 640, y < 480); bit 7 of the byte is the leftmost pixel.
$B00001 write: b0 video on, b1 page shown (reset: 0, screen black, page 0). Read: b0 VBLANK, b1 HBLANK. The register repeats over $B00001-$BFFFFF.
U1 cpld/rsv_u1.pld, U2 cpld/rsv_u2.pld -- both ATF1502AS-10JU44 (CUPL; WinCUPL + fitter, one JTAG chain on J3). VGA 640x480 @ 60 Hz from 25.000 MHz: 100 bytes per line, HSYNC byte times 83-94, VSYNC lines 490-491.

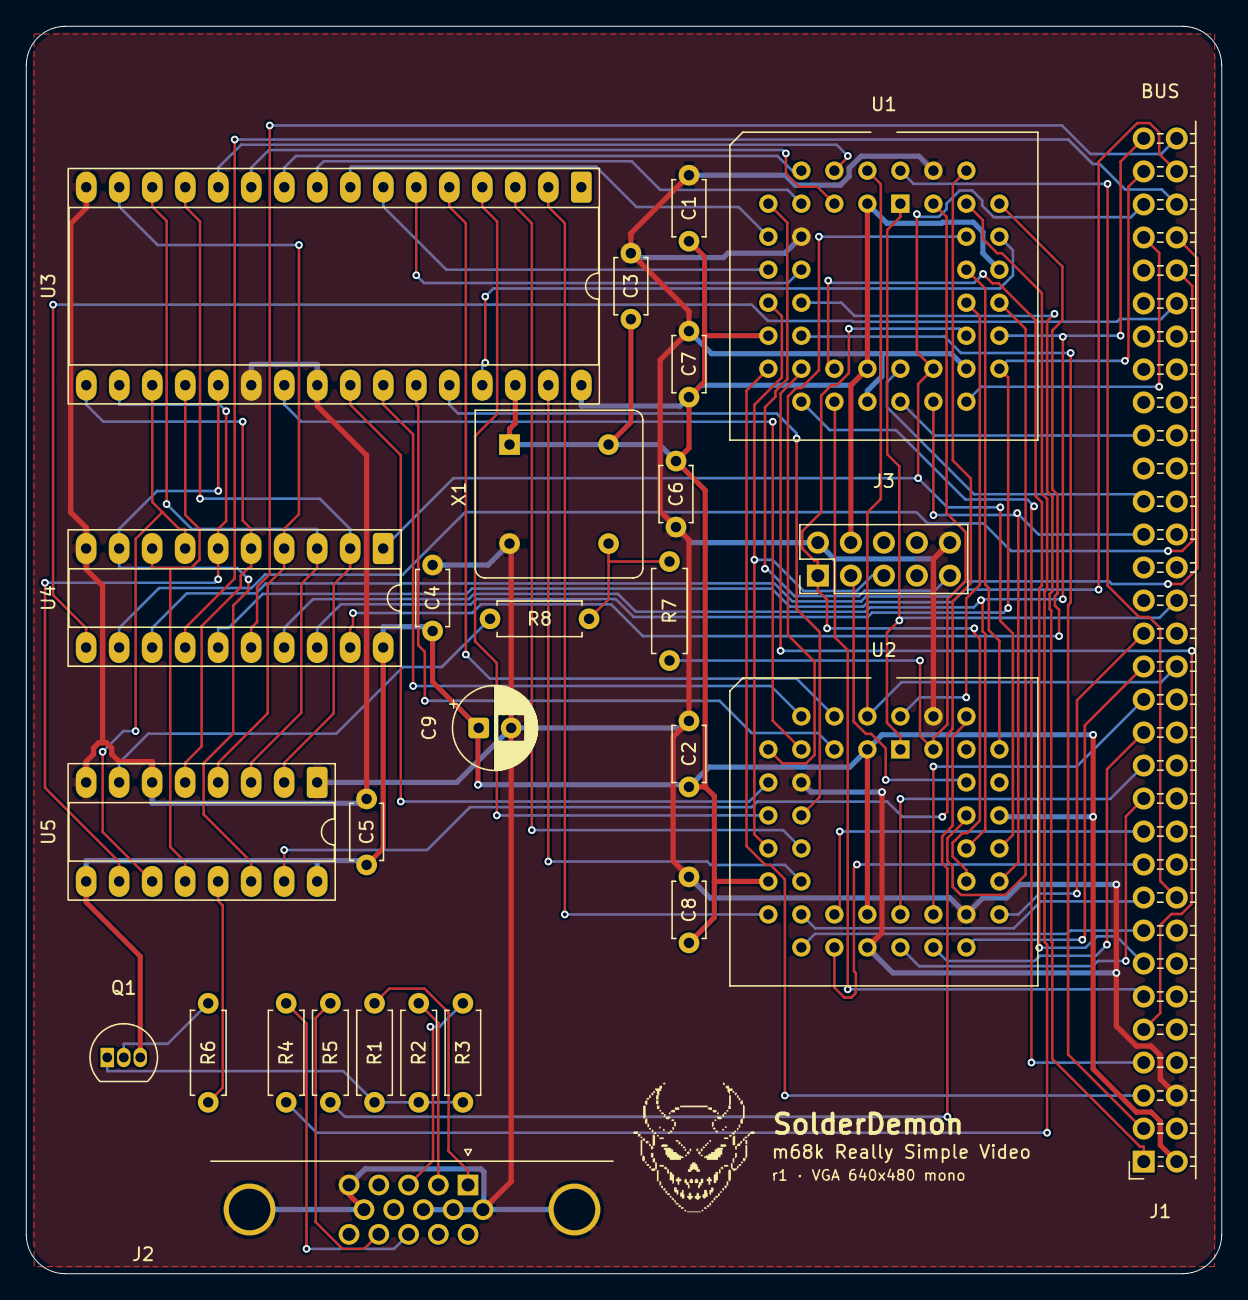
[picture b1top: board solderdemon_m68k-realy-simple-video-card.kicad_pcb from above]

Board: 2 copper layers, 92.0 x 96.0 mm, 28 parts (0 on the bottom side), 84 nets.

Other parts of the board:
LOGO1: SolderDemon_Logo

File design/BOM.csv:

Reference,Value,Footprint
J1,SOLDERDEMON M68K BUS,SolderDemonReallySimpleVideo:PinSocket_2x32_P2.54mm_Horizontal_CardEdge
U1,ATF1502AS-10JU44,Package_LCC:PLCC-44_THT-Socket
U2,ATF1502AS-10JU44,Package_LCC:PLCC-44_THT-Socket
J3,JTAG,Connector_PinHeader_2.54mm:PinHeader_2x05_P2.54mm_Vertical
U3,AS6C1008-55PCN,Package_DIP:DIP-32_W15.24mm_Socket_LongPads
U4,74HCT245,Package_DIP:DIP-20_W7.62mm_Socket_LongPads
U5,74HC166,Package_DIP:DIP-16_W7.62mm_Socket_LongPads
X1,25.000MHz,Oscillator:Oscillator_DIP-8
R6,220,Resistor_THT:R_Axial_DIN0207_L6.3mm_D2.5mm_P7.62mm_Horizontal
Q1,2N3904,Package_TO_SOT_THT:TO-92_Inline
R1,390,Resistor_THT:R_Axial_DIN0207_L6.3mm_D2.5mm_P7.62mm_Horizontal
R2,390,Resistor_THT:R_Axial_DIN0207_L6.3mm_D2.5mm_P7.62mm_Horizontal
R3,390,Resistor_THT:R_Axial_DIN0207_L6.3mm_D2.5mm_P7.62mm_Horizontal
R4,47,Resistor_THT:R_Axial_DIN0207_L6.3mm_D2.5mm_P7.62mm_Horizontal
R5,47,Resistor_THT:R_Axial_DIN0207_L6.3mm_D2.5mm_P7.62mm_Horizontal
R7,33,Resistor_THT:R_Axial_DIN0207_L6.3mm_D2.5mm_P7.62mm_Horizontal
R8,33,Resistor_THT:R_Axial_DIN0207_L6.3mm_D2.5mm_P7.62mm_Horizontal
J2,VGA,SolderDemonReallySimpleVideo:DSUB-15-HD_Socket_Horizontal_P2.29x1.90mm_EdgePinOffset3.03mm_Housed_MountingHolesOffset4.94mm
C1,100nF,SolderDemonCaps:C_Radial_5.08mm
C2,100nF,SolderDemonCaps:C_Radial_5.08mm
C3,100nF,SolderDemonCaps:C_Radial_5.08mm
C4,100nF,SolderDemonCaps:C_Radial_5.08mm
C5,100nF,SolderDemonCaps:C_Radial_5.08mm
C6,100nF,SolderDemonCaps:C_Radial_5.08mm
C7,100nF,SolderDemonCaps:C_Radial_5.08mm
C8,100nF,SolderDemonCaps:C_Radial_5.08mm
C9,47uF 10V,Capacitor_THT:CP_Radial_D6.3mm_P2.50mm
